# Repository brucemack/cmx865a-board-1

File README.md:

Overview
========

A basic breakout board for the CMX865A modem IC.  Device [datasheet is here](https://www.mouser.com/datasheet/2/976/CMX865A_ds-1591712.pdf).

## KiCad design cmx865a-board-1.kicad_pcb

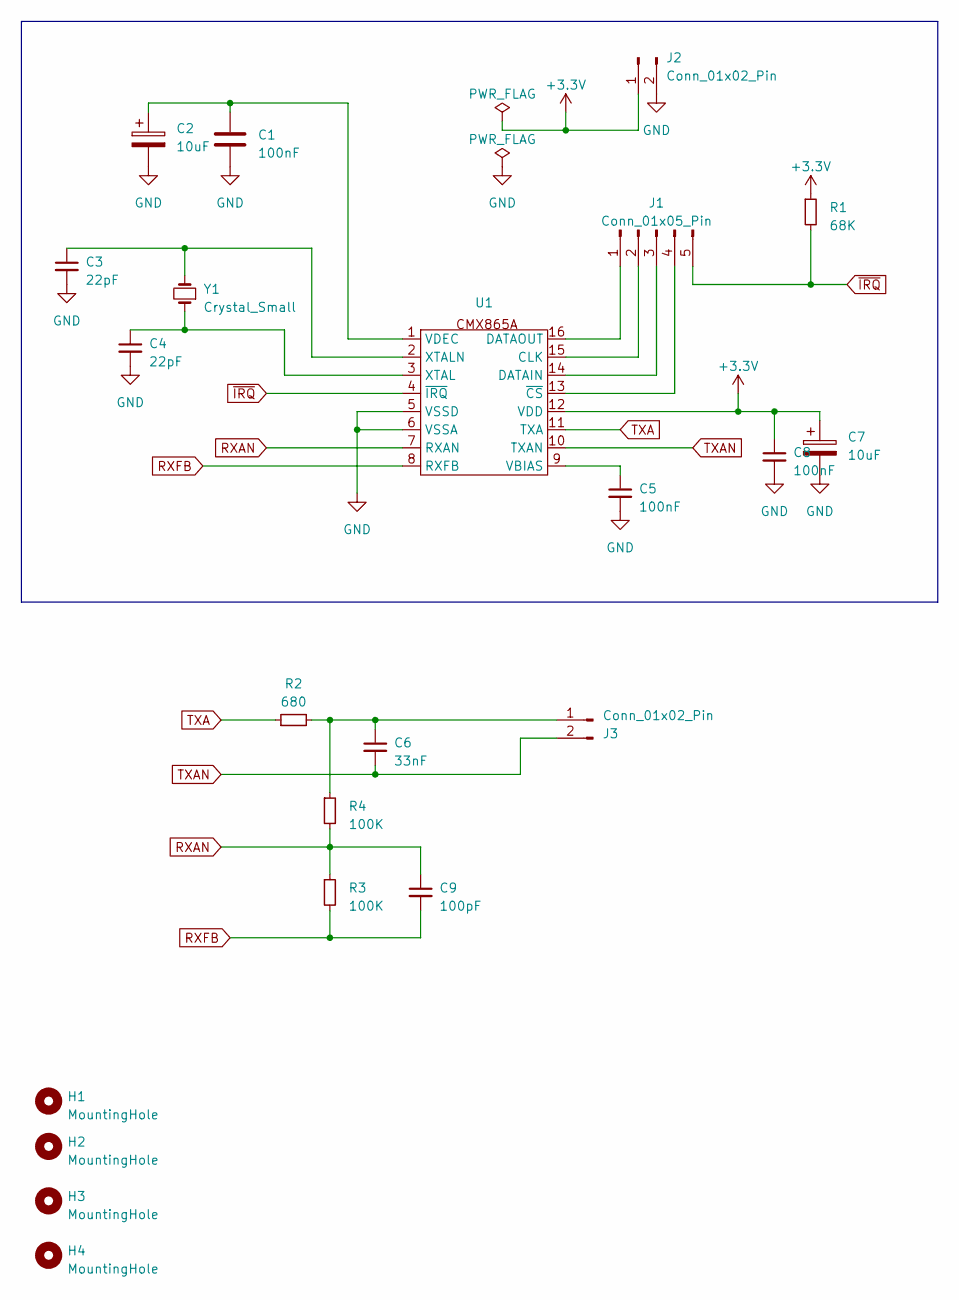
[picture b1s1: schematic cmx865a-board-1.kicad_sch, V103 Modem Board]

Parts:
C1, C5, C8: 100nF; C_0805_2012Metric_Pad1.18x1.45mm_HandSolder
C2, C7: 10uF; CP_Radial_D5.0mm_P2.50mm
C3, C4: 22pF; C_0805_2012Metric_Pad1.18x1.45mm_HandSolder
C6: 33nF; C_0805_2012Metric_Pad1.18x1.45mm_HandSolder
C9: 100pF; C_0805_2012Metric_Pad1.18x1.45mm_HandSolder
H1, H2, H3, H4: MountingHole; MountingHole_4mm
J1: Conn_01x05_Pin; PinHeader_1x05_P2.54mm_Vertical
J2, J3: Conn_01x02_Pin; PinHeader_1x02_P2.54mm_Vertical
R1: 68K; R_0805_2012Metric_Pad1.20x1.40mm_HandSolder
R2: 680; R_0805_2012Metric_Pad1.20x1.40mm_HandSolder
R3, R4: 100K; R_0805_2012Metric_Pad1.20x1.40mm_HandSolder
U1: SOIC-16W_7.5x12.8mm_P1.27mm
Y1: Crystal_Small; Crystal_HC49-U_Vertical

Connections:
+3.3V: C7.1, C8.1, J2.1, R1.1, U1.12 (VDD)
GND: C1.2, C2.2, C3.2, C4.2, C5.2, C7.2, C8.2, J2.2, U1.5 (VSSD), U1.6 (VSSA)
unnamed: J1.1, U1.16 (DATAOUT)
unnamed: J1.2, U1.15 (CLK)
unnamed: J1.3, U1.14 (DATAIN)
unnamed: J1.4, U1.13 (~CS)
unnamed: C6.1, J3.1, R2.2, R4.1
unnamed: C5.1, U1.9 (VBIAS)
unnamed: C1.1, C2.1, U1.1 (VDEC)
unnamed: C4.1, U1.3 (XTAL), Y1.1
unnamed: C3.1, U1.2 (XTALN), Y1.2
RXAN: C9.1, R3.1, R4.2, U1.7 (RXAN)
RXFB: C9.2, R3.2, U1.8 (RXFB)
TXA: R2.1, U1.11 (TXA)
TXAN: C6.2, J3.2, U1.10 (TXAN)
~IRQ: J1.5, R1.2, U1.4 (~IRQ)

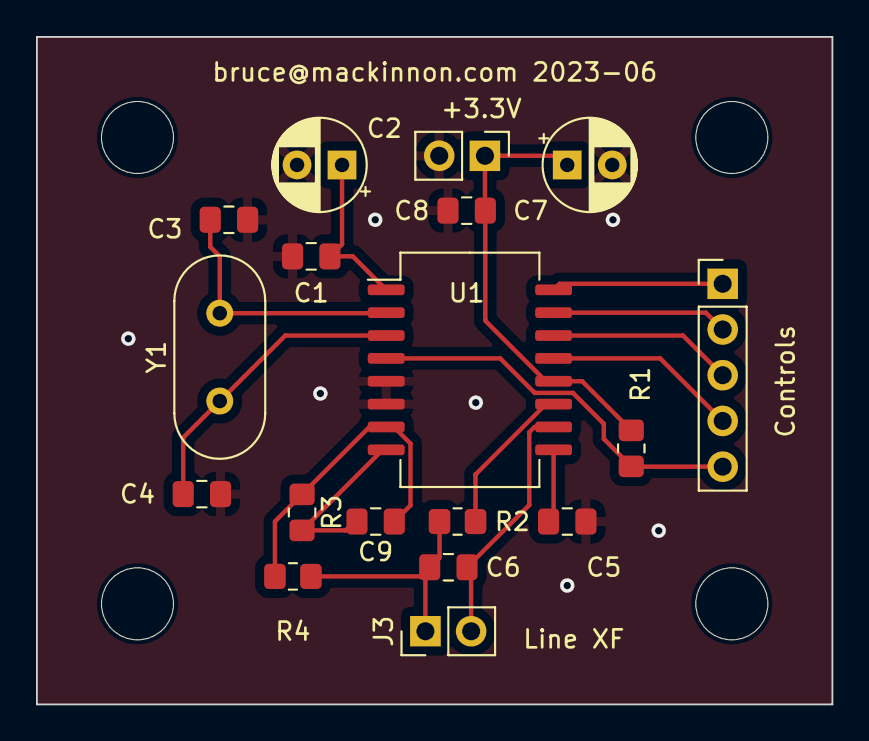
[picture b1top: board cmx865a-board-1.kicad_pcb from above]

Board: 2 copper layers, 44.2 x 37.1 mm, 22 parts (0 on the bottom side), 16 nets.
